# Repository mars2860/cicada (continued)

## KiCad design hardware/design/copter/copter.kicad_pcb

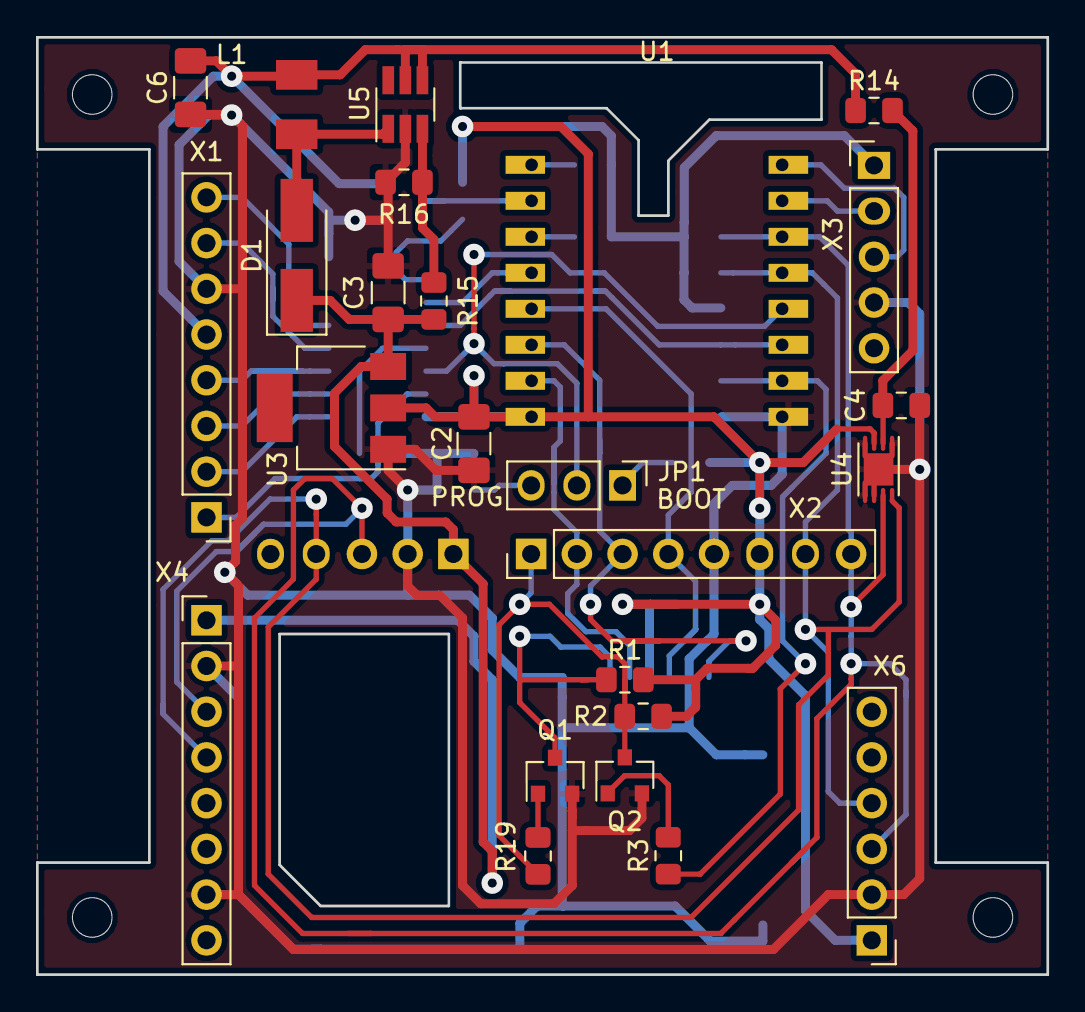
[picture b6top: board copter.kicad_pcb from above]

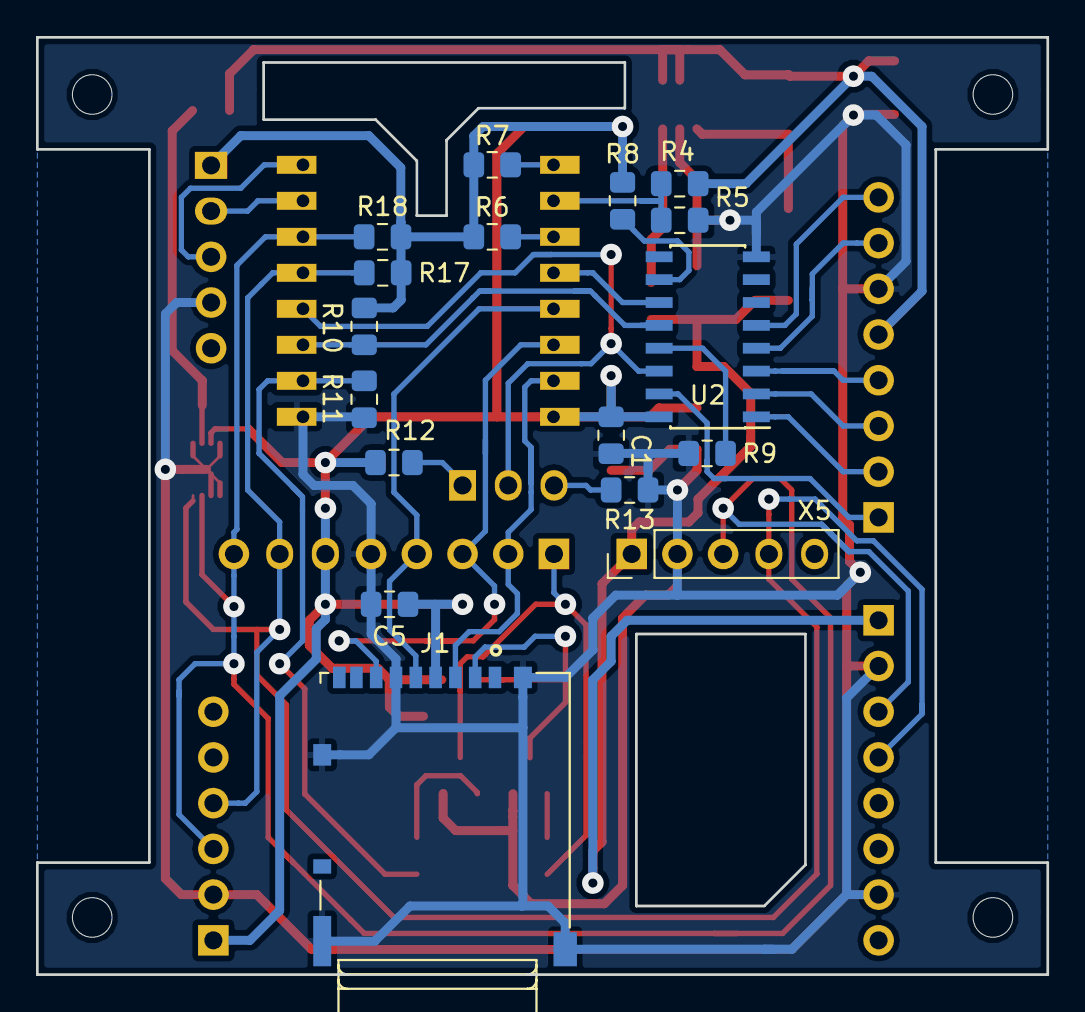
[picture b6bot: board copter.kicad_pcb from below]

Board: 2 copper layers, 56.1 x 52.1 mm, 42 parts (17 on the bottom side), 35 nets.

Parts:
C1, C5: 100 nF; C_0805_2012Metric_Pad1.15x1.40mm_HandSolder
C2, C3, C6: 20 uF; C_1206_3216Metric_Pad1.42x1.75mm_HandSolder
C4: 1 uF; C_0805_2012Metric_Pad1.15x1.40mm_HandSolder
D1: SS34; D_SMA_Handsoldering
J1: DM3AT-SF-PEJM5; HRS_DM3AT-SF-PEJM5
JP1: Jumper_3_Bridged12; PinHeader_1x03_P2.54mm_Vertical
L1: SPM4020T-4R7; SPM4020T
Q1, Q2: BSS138; SOT-23
R1, R2, R5, R8, R9: 33k; R_0805_2012Metric_Pad1.15x1.40mm_HandSolder
R3, R6, R7, R10, R11, R12, R13, R17, R18, R19: 3k3; R_0805_2012Metric_Pad1.15x1.40mm_HandSolder
R4: 110k; R_0805_2012Metric_Pad1.15x1.40mm_HandSolder
R14: 1k; R_0805_2012Metric_Pad1.15x1.40mm_HandSolder
R15: 160k; R_0805_2012Metric_Pad1.15x1.40mm_HandSolder
R16: 22k; R_0805_2012Metric_Pad1.15x1.40mm_HandSolder
U1: ESP-07
U2: 74HC595; SOIC-16_3.9x9.9mm_P1.27mm
U3: LM1117-3.3; SOT-223-3_TabPin2
U4: MAX17040; TDFN-8-1EP_3x2mm_P0.5mm_EP1.80x1.65mm
U5: MT3608; SOT-23-6_Handsoldering
X1: ESC; PinHeader_1x08_P2.54mm_Vertical
X2: Arducam; PinHeader_1x08_P2.54mm_Vertical
X3: UART; PinHeader_1x05_P2.54mm_Vertical
X4: MPU-6050; GY-521
X5: HMC5883L; GY-273
X6: BMP280; GY-BMP280

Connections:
+3V3: C1.1, C2.1, C5.1, J1.4, R1.1, R2.1, R6.1, R7.1, R8.1, R10.1, R12.1, R17.1, R18.1, U1.8, U2.16, U3.2, U4.3, X2.6, X3.1, X6.1
+5V: C3.1, D1.1, R15.1, U3.3, X4.1, X5.1
+BATT: C6.1, L1.2, R4.1, R14.1, U5.4, U5.5, X1.5
/CLOCK: U1.4, U2.11
/CS0: Q2.3, R2.2, R19.1, X2.1
/CS1: J1.2, Q1.3, R1.2
/LATCH: R10.2, U1.11, U2.12
/LED1: U2.4, X1.7
/LED2: U2.5, X1.8
/M1: U2.15, X1.1
/M2: U2.1, X1.2
/M3: U2.2, X1.3
/M4: U2.3, X1.4
/MISO: J1.7, U1.6, X2.3
/MOSI: J1.3, U1.7, X2.2
/RXD: U1.16, X3.3
/SCK: J1.5, U1.5, X2.4
/SHIFT: JP1.2, U1.12, U2.14
/TXD: U1.15, X3.2
/~CAM\~SD: R3.2, R11.1, U1.10
GNDD: C1.2, C2.2, C3.2, C4.2, C5.2, C6.2, J1.6, J1.P1, J1.P2, J1.P3, J1.P4, Q1.2, Q2.2, R5.2, R9.2, R11.2, R13.2, R16.2, U1.9, U2.8, U3.1, U4.1, U4.4, U4.5, U4.6, U4.9, U5.2, X1.6, X2.5, X3.4, X4.2, X4.7, X5.2, X6.2
unnamed: C4.1, R14.2, U4.2
unnamed: D1.2, L1.1, U5.1
unnamed: JP1.1, R12.2
unnamed: JP1.3, R13.1
unnamed: Q1.1, R19.2
unnamed: Q2.1, R3.1
unnamed: R4.2, R5.1, U1.2
unnamed: R6.2, U1.3
unnamed: R7.2, U1.1
unnamed: R8.2, U2.10
unnamed: R9.1, U2.13
unnamed: R15.2, R16.1, U5.3
SCL: R18.2, U1.14, U4.7, X2.8, X4.3, X5.3, X6.3
SDA: R17.2, U1.13, U4.8, X2.7, X4.4, X5.4, X6.4

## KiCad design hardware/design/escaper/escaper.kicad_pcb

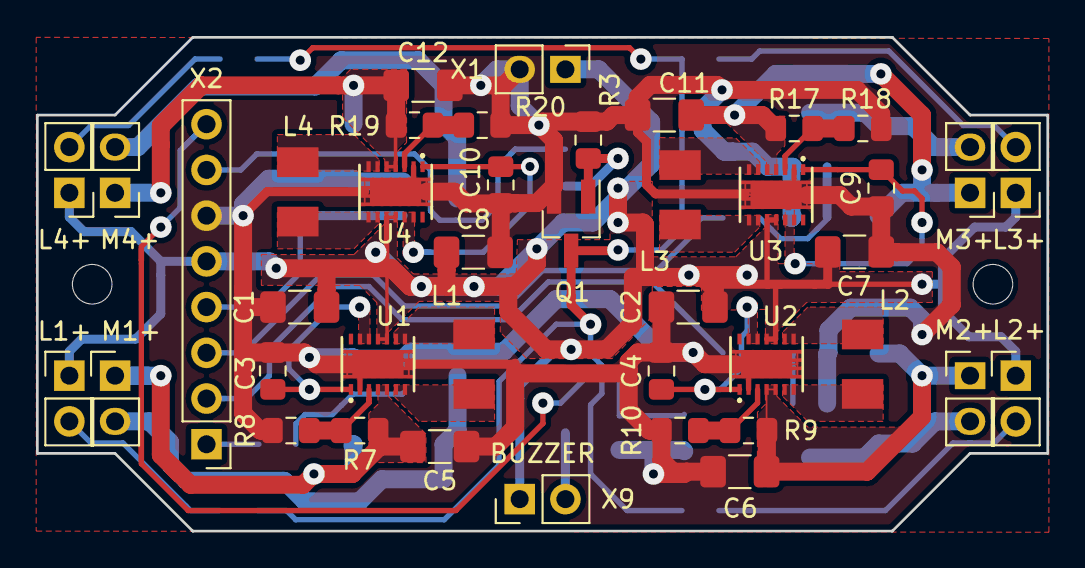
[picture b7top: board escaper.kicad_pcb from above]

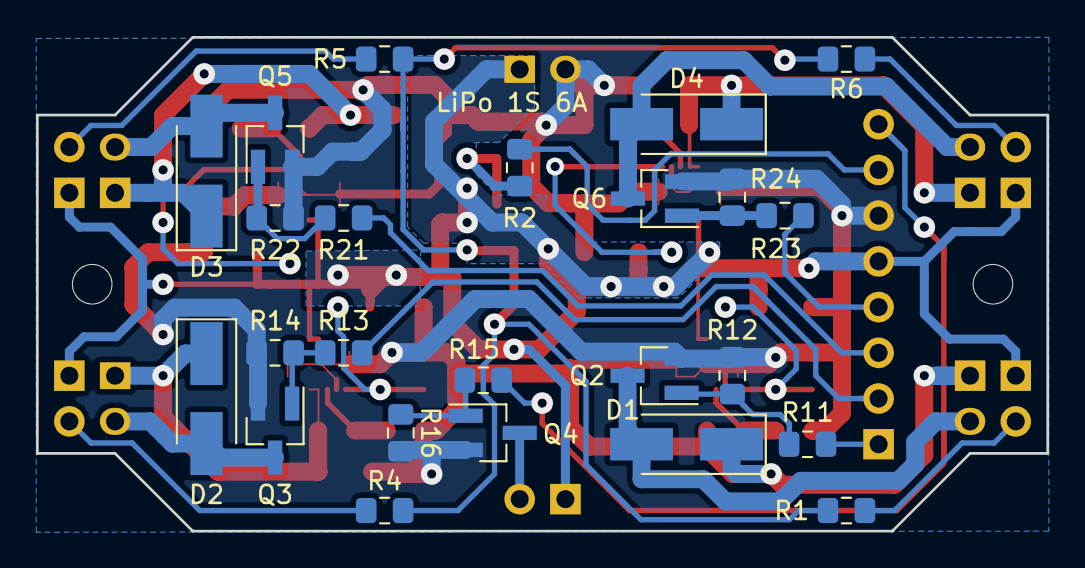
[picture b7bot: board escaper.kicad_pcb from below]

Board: 2 copper layers, 56.1 x 27.4 mm, 65 parts (24 on the bottom side), 44 nets.

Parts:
C1, C2, C5, C6, C7, C8, C11, C12: C_1206_3216Metric_Pad1.42x1.75mm_HandSolder
C3, C4, C9, C10: C_0805_2012Metric_Pad1.15x1.40mm_HandSolder
D1, D2, D3, D4: D_SMA_Handsoldering
L1, L2, L3, L4: SPM4020T
Q1, Q2, Q3, Q4, Q5, Q6: SOT-23_Handsoldering
R1, R2, R3, R4, R5, R6, R7, R8, R9, R10, R11, R12, R13, R14, R15, R16, R17, R18, R19, R20, R21, R22, R23, R24: R_0805_2012Metric_Pad1.15x1.40mm_HandSolder
U1, U2, U3, U4: VSON-14
X1: LiPo 1S 6A; PinHeader_1x02_P2.54mm_Vertical
X2: PinHeader_1x08_P2.54mm_Vertical
X3: L1+; PinHeader_1x02_P2.54mm_Vertical
X4: L2+; PinHeader_1x02_P2.54mm_Vertical
X5: L3+; PinHeader_1x02_P2.54mm_Vertical
X6: L4+; PinHeader_1x02_P2.54mm_Vertical
X7: M1+; PinHeader_1x02_P2.54mm_Vertical
X8: M2+; PinHeader_1x02_P2.54mm_Vertical
X9: BUZZER; PinHeader_1x02_P2.54mm_Vertical
X10: M3+; PinHeader_1x02_P2.54mm_Vertical
X11: M4+; PinHeader_1x02_P2.54mm_Vertical

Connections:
+BATT: C1.1, C2.1, C7.1, C8.1, U1.10, U1.11, U2.10, U2.11, U3.10, U3.11, U4.10, U4.11, X1.1, X2.5, X3.1, X4.1, X5.1, X6.1, X9.1
BUZ: R15.2, X2.8
GNDD: C1.2, C2.2, C3.2, C4.2, C5.2, C6.2, C7.2, C8.2, C9.2, C10.2, C11.2, C12.2, Q1.2, Q2.2, Q3.2, Q4.2, Q5.2, Q6.2, R3.2, R8.2, R10.2, R12.2, R14.2, R16.2, R18.2, R20.2, R22.2, R24.2, U1.2, U1.15, U1.16, U1.17, U1.18, U1.19, U1.20, U1.21, U1.22, U1.23, U2.2, U2.15, U2.16, U2.17, U2.18, U2.19, U2.20, U2.21, U2.22, U2.23, U3.2, U3.15, U3.16, U3.17, U3.18, U3.19, U3.20, U3.21, U3.22, U3.23, U4.2, U4.15, U4.16, U4.17, U4.18, U4.19, U4.20, U4.21, U4.22, U4.23, X1.2, X2.6
LED: R2.2, X2.7
M1: R11.1, X2.1
M2: R13.1, X2.2
M3: R21.1, X2.3
M4: R23.1, X2.4
unnamed: C3.1, U1.1, U1.12, U1.13
unnamed: C4.1, U2.1, U2.12, U2.13
unnamed: C5.1, D1.1, R7.1, U1.4, U1.5, X7.1
unnamed: C6.1, D2.1, R9.1, U2.4, U2.5, X8.1
unnamed: C9.1, U3.1, U3.12, U3.13
unnamed: C10.1, U4.1, U4.12, U4.13
unnamed: C11.1, D3.1, R17.1, U3.4, U3.5, X10.1
unnamed: C12.1, D4.1, R19.1, U4.4, U4.5, X11.1
unnamed: D1.2, Q2.3, X7.2
unnamed: D2.2, Q3.3, X8.2
unnamed: D3.2, Q5.3, X10.2
unnamed: D4.2, Q6.3, X11.2
unnamed: L1.1, U1.8, U1.9
unnamed: L1.2, U1.6, U1.7
unnamed: L2.1, U2.8, U2.9
unnamed: L2.2, U2.6, U2.7
unnamed: L3.1, U3.8, U3.9
unnamed: L3.2, U3.6, U3.7
unnamed: L4.1, U4.8, U4.9
unnamed: L4.2, U4.6, U4.7
unnamed: Q1.1, R2.1, R3.1
unnamed: Q1.3, R1.2, R4.2, R5.2, R6.2
unnamed: Q2.1, R11.2, R12.1
unnamed: Q3.1, R13.2, R14.1
unnamed: Q4.1, R15.1, R16.1
unnamed: Q4.3, X9.2
unnamed: Q5.1, R21.2, R22.1
unnamed: Q6.1, R23.2, R24.1
unnamed: R1.1, X3.2
unnamed: R4.1, X4.2
unnamed: R5.1, X5.2
unnamed: R6.1, X6.2
unnamed: R7.2, R8.1, U1.3
unnamed: R9.2, R10.1, U2.3
unnamed: R17.2, R18.1, U3.3
unnamed: R19.2, R20.1, U4.3

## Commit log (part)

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2019-09-04 Первая версия с работающей электроникой и работающим управлением двигателями
2019-09-05 Добавил в пульт управления панели Alarms и Settings
2019-09-06 Перенес настройки в отдельный диалог и сделал сохранение/загрузку настроек
2019-09-06 1. Перенес классы команд в пакет copter 2. Добавил класс для приёма телеметрических данных 3. Поправил пользовательский интерфейс диалога настроек 4. Отладил работу сообщений об авариях
2019-09-06 Доработал панель управления моторами
2019-09-10 1. Добавил в пульт класс слайдера для управления газом мотора 2. Добавил в прошивку чтение max17040 и отправку данных на хост 3. Сделал обработку данных от max17040 на стороне хоста
2019-09-11 1. Добавил в телеметрию RSSI, Accel, Gyro с отправкой и визуализацией на ПК 2. Перенес библиотеки для софта в папку проекта
2019-09-12 Добавил в телеметрию показания магнетометра и смещение для акселерометра, гироскопа
2019-09-13 Сделал визуализацию сырых данных от акселерометра и магнетометра для анализа калибровки
2019-09-13 Перенес настройки в отдельный класс
2019-09-14 Реализовал процесс калибровки датчиков, передачи калибровки в коптер, сохранение калибровки на стороне хоста
2019-09-14 Поправил количество циклов в калибровке акселерометра и гироскопа
2019-09-16 Добавил в телеметрию крен, тангаж, рысканье и азимут
2019-09-17 Уменьшил время опроса датчиков по I2C с 88 мс до 1-5 мс
2019-09-18 Сделал компенсацию углов наклона для компаса
2019-09-22 Добавил диалог подтверждения сохранения калибровки датчиков при закрытии окна датчиков
2019-09-22 Обрезал пустое пространство в иконках YPR
2019-09-22 Добавил горизонтальный слайдер для управления газом двигателя
2019-09-22 Уменьшил паузу между командами до 50 мс
2019-09-26 Сделал нормальную синхронизацию слайдера управления двигателем
2019-09-27 Сделал всю инфраструктуру для ПИД: настройка, сохранение параметров, передача на коптер, визуализация и пр.
2019-09-28 Изменил сважность ШИМ двигателя с 256 до 1000 и переделал команду для передачи уровня газа
2019-10-01 В процессе работа над ПИД
2019-10-03 Стабилизация по углам плохо, но работает
2019-10-14 Много изменений, но главное необходимо выкинуть из схемы регистр 595 и управлять двигателями напрямую с ног МК. Тема для новой ветки
2019-10-17 Переделал PWM на частоту 500 Гц с разрешением 2000
2019-10-17 Переделал алгоритм калибровки магнетометра на хосте, чтобы работало на Java7
2019-10-19 1. Перевёл проект прошивки в SloeberIDE 2. Переделал обновление прошивки на протокол HTTP 3. Изменил в протоколе формат данных для напряжения и процента батареи
2019-11-06 1. Сделал раму под TEENYPRO ESCAPER и двигатели 0703 2. Реализовал протокол DSHOT300 3. Различные эксперименты с PWM, высотой и др.
2019-12-16 Добавил библиотеку rtimulib2
2019-12-17 Добавил команду TakeOff для резкого взлета коптера
2019-12-17 Переделал окно датчиков на Frame, добавил кнопку для сброса компаса, убрал кнопки для расчета калибровки акселерометра и гироскопа на хосте
2019-12-17 1. Вернулся к PWM 2. Сделал не симметричный ПИД, когда ПИД при изменении углов управляет только двигателями с одной стороны
2019-12-17 Обновил выводы
2020-04-16 Если в rtimulib включен компас, то отправляем его данные на хост, если нет, то считаем направление своим алгоритмом
2020-04-20 Работа над первой комплируемой версией pdl в процессе
2020-04-20 Первая откомпилированная версия
2020-04-25 1. Отладил алгоритм PDL. Теперь всё работает как было до этого 2. Обновил драйвер mpu6050 3. Исправил ошибку в драйвере mpu6050 в алгоритме калбировки акселерометра
2020-05-22 Сделал базовый класс для всех окон. Базовый класс умеет сохранять положение и размеры окна в файл настроек. Перенес интерфейс для управления моторами в отдельное окно. Добавил иконки для главных кноп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
2020-05-23 Перенес интерфейс состояния дрона в отдельное окно. Добавил механизм для получения текста или иконки из любой части приложения
2020-12-28 Вернулся к dshot из-за поломки двигателей 8520
2020-12-28 Переход на новый дизайн управляющей программы
2020-12-28 Добавил инициализацию портов ввода-вывода для dshot-escaper
2021-01-06 Изменил тип рамы в PDL на крестовую раму
2021-01-06 Поправил изменение газа для каждого двигателя после того как был изменен общий раз
2021-01-09 Вынес DroneState в самостоятельный класс
2021-01-09 Сделал построение дерева настроек по классу DroneState
2021-01-09 Сделал сохранение настроек в файл JSON
2021-01-11 1. Сделал редактирование, сохранение и отправку настроек 2. В DroneState избавился от лишних классов для ПИД и гироскопа
2021-01-11 Добавил окно RemoteControl
2021-01-29 Исправил баг, мешавший вводить отрицательное число в поле ввода
2021-02-22 1. Модифицировал прошивку под новую плату 2. Исправилял баги 3. Добился успешной работы ПИД для yaw
2021-10-14 Добавил скользящее среднее для периода выполнения основного цикла прошивки
2021-10-14 Вычисление состояния батарейки по данным АЦП
2021-10-15 Сделал пошаговоый ПИД для стабилизации
2021-10-17 Сделал максимальный газ для двигателя 1999, так как при 2000 двигатели клинило. Добавил в ПИД ограничение на максимальное выходное значение
2021-10-17 Добавил забытые файлы
2021-10-18 Добавил кнопку для сброса данных из черного ящика
2021-10-20 Прикрутил лидар vl53l1x
2021-10-22 Прикрутил оптический датчик смещения и отладил работу altPid
2021-10-27 Добился более-менее хорошей стабилизации по оптическому датчику смещения, но код ещё грязный
2021-10-27 Изменил модель данных, добавил ПИД для вертикальной скорости, но успеха не добился и вернулся к старому AltPid. ПИД для вертикальной скорости пока решил оставить
2021-11-03 Рефакторинг PDL, добавил документацию для PDL, отрефакторил координатные оси и номера двигателей в соответствии с документацией
2021-11-03 Переделал картинки для документации PDL в формат SVG
2021-11-03 Забыл положить в репозиторий новые картинки для документации PDL
2021-11-07 Добавил ПИД для управления вертикальной скоростью в цепочку ПИД перед AltPID
2021-11-07 Большой рефакторинг названий переменных, классов, файлов и папок
2021-11-07 edit readme
2021-11-08 Добавил в репозиторий 3д-модель рамы из деревянной линейки под двигатели 0703
2021-11-08 Добавил в репозиторий проектные файлы "железа"
2021-11-08 Забыл добавить файлы библиотек для KiCad
2021-11-09 Поправил систему координат
2021-11-09 Рефакторинг названия класса приложения
2021-11-09 Перенес sensor-fusion из main.c в imu_mpu6550.c
2021-11-09 Исправил YawPitchRoll, OpticalFlow X&Y, ПИДы в соответствии с принятой системой координат
2021-11-09 Исправил калибровку трех-осевых датчиков, используя desktop приложение
2021-11-10 Добавил картинки в файл readme
2024-04-18 added 3d models for some electronic components
2024-04-18 added some components to kicad libs
2024-04-18 added new board cicada-gy91-v3
2024-04-18 added new board cicada-main-v4
2024-04-18 added new board cicada-micro-v2
2024-04-18 added new board cicada-pwm-esc-v3
2024-04-18 deleted deprecated drone model cicada-se0703-wood-frame
2024-04-25 Added cicada-1404 drone
2024-04-26 Added KV units of motors to description of cicada-1404
2024-04-27 Added cicada-0802 quadcopter
2024-05-03 added notification to sold power jumper in cicada-0802-electrical-schematic
2024-05-03 added gemfan 1609 propeller to cicada-0802 readme
2024-05-06 Added quadcopter cicada-1106
2024-05-07 Added cicada-0816df drone
2024-05-07 Added signature to electrical schematics
2024-05-08 Added new version of firmware (v2)
2024-05-08 Added new version of desktop software v2
2024-05-08 Added mobile app v1
2024-05-08 Added russian manual
2024-05-09 Updated cicada-manual-ru
2024-05-09 Updated readme file
2024-05-09 Increase dead zone for gamepad in mobile application
2024-05-09 orthography
2024-05-15 Added firmware project settings
2024-05-15 Added native libraries for software project and settings of software project
2024-05-16 Fix a bug of control drone altitude by gas
2024-05-26 Fixed chapter 10. Input devices poll time is 40 ms (25Hz)
2024-05-26 Updated firmware project files
2024-05-26 Added fiberglass frame for cicada-0802
2024-05-26 Commands queue has been changed from LIFO to FIFO
2024-05-26 Added new version name for desktop application
2024-05-26 Input devices poll time has been reduced from 20 ms to 40 ms because on some mobile devices there was lags in control. Added version name to MainActivity
2024-05-30 Added CNC path to cut off protection legs from fiberglass
2024-05-30 Added velUpOffset parameter
2024-05-30 Fixed checking supported firmware and changed supporting to PDL v3
2024-05-30 Changed firmware and PDL version to v3
2024-05-30 Added delay 3s to wait loading default settings when we press LoadDefault button
2024-05-30 Changed parameter velUpOffset to accUpOffset
2024-05-30 Increased delay to 5s to wait applying default settings
2024-05-30 Clear log when connecting to the drone
2024-05-30 Fixed memory leaks when load default command is received
2024-06-09 Added new feature to compensate baseGas when battery gets low
2024-06-09 Added links to parts
2024-06-09 Added case for camera eachine tx06
2024-06-09 Added lighter case for camera akk ba3
2024-06-09 Added holders for battery LiHv gnb-380
2024-06-09 Fixed feature preventing flying away
2024-06-09 Fixed connecting to target and default wifi net
2024-06-09 Fixed output of lat,lon,sat
2024-06-25 Added a reversed cross-frame
2024-06-25 Added a description of a reversed cross-frame
2024-08-07 Updated DroneLog to latest version of desktop app
2024-08-07 Added CmdSetAccUpOffset
2024-08-07 Done that rotate delta in trickmode is not changed to trickmode delta if we have rotateBy=ROTATE_BY_YAW_RATE. It's changed switching to trickmode by single button pressing instead of button holding
2024-08-13 Moved speaking of a DroneState to the pdl-classes layer, added the sounds group to a DroneState
2024-08-13 Added the java pdl-classes to the own folder
2024-08-13 Added the implementation of SoundProvider
2024-08-13 Added bat1.wav sound
2024-08-13 Changed playing of stabilization_disabled.wav to playing with delay 2s after motors_disabled.wav
2024-08-13 Removed the local copy of pdl classes and added the source folder link to software/libs/pdlJavaClasses
2024-08-30 Refactoring - moved the telemetryPeriod param to the DroneState structure
2024-09-02 Added pitchAutoLevel and rollAutoLevel
2024-09-03 Added the drone control by body angular rates
2024-09-06 Refactored the trick mode
2024-09-06 Fixed switching to a trick mode in mobile app
2024-09-09 Added pdlWorldToBody
2024-10-14 Added wifi broadcast mode
2024-10-17 Refactored saving wifi settings at the drone side
2024-10-17 Refactored the mechanism to avoid collisions in radio between two drones work at the same channel
2024-10-17 Added statistics for wlan rx/tx packets
2024-10-18 Fixed mobile app due latest changes of pdlJavaClasses
2024-10-20 wip: try to measure the net latency but something in firmware bricks the drone
2024-10-20 Added measuring of net latency
2024-10-21 working around the problem: we can't connect to softAp from some smarthphones and PCs
2024-10-21 Fixed: the system resets when we try to switch back to wifi normal mode
2024-10-22 Added the serial port driver for Android application and bug fixing
2024-10-28 Bug fixing around WifiBroadcast mode
2024-10-28 Changed default WiFi mode to STA because some devices can't communicate with ESP softAP
2024-10-29 Refactored debug with output to Serial
2024-10-30 Fixed: low radio signal is not spoken when the drone is in WIFI_AP mode
2024-10-30 Fixed: runcam is not found
2024-11-07 Updated version to 3 and bug fixing
2024-11-07 Added net latency and lostRxPackets to Widgets
2024-11-11 Updated drone settings
2024-11-11 Updated manual
2024-11-11 Added new drone cicada-0802-star
2024-11-23 Added supporting of XIAO_ESP32S3 module
2024-12-06 Added jpeg streaming for xiao_esp32s3 and jpeg stream rendering in desktop application
2024-12-09 Implemented playing video stream in android app using Canvas
2024-12-09 Implemented split screen for VR
2024-12-10 Speed up camera FPS
2024-12-22 The first flying version of cicada32
2024-12-24 Working version with hx-esp32-camera driver allowing 800x600 at 30FPS
2024-12-24 updated drone configs
2024-12-24 Reinforced the case for eachine tx06 camera
